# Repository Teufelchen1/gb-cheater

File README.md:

# gb-cheater
A gameboy(GB,GBC,GBA) reader/writer

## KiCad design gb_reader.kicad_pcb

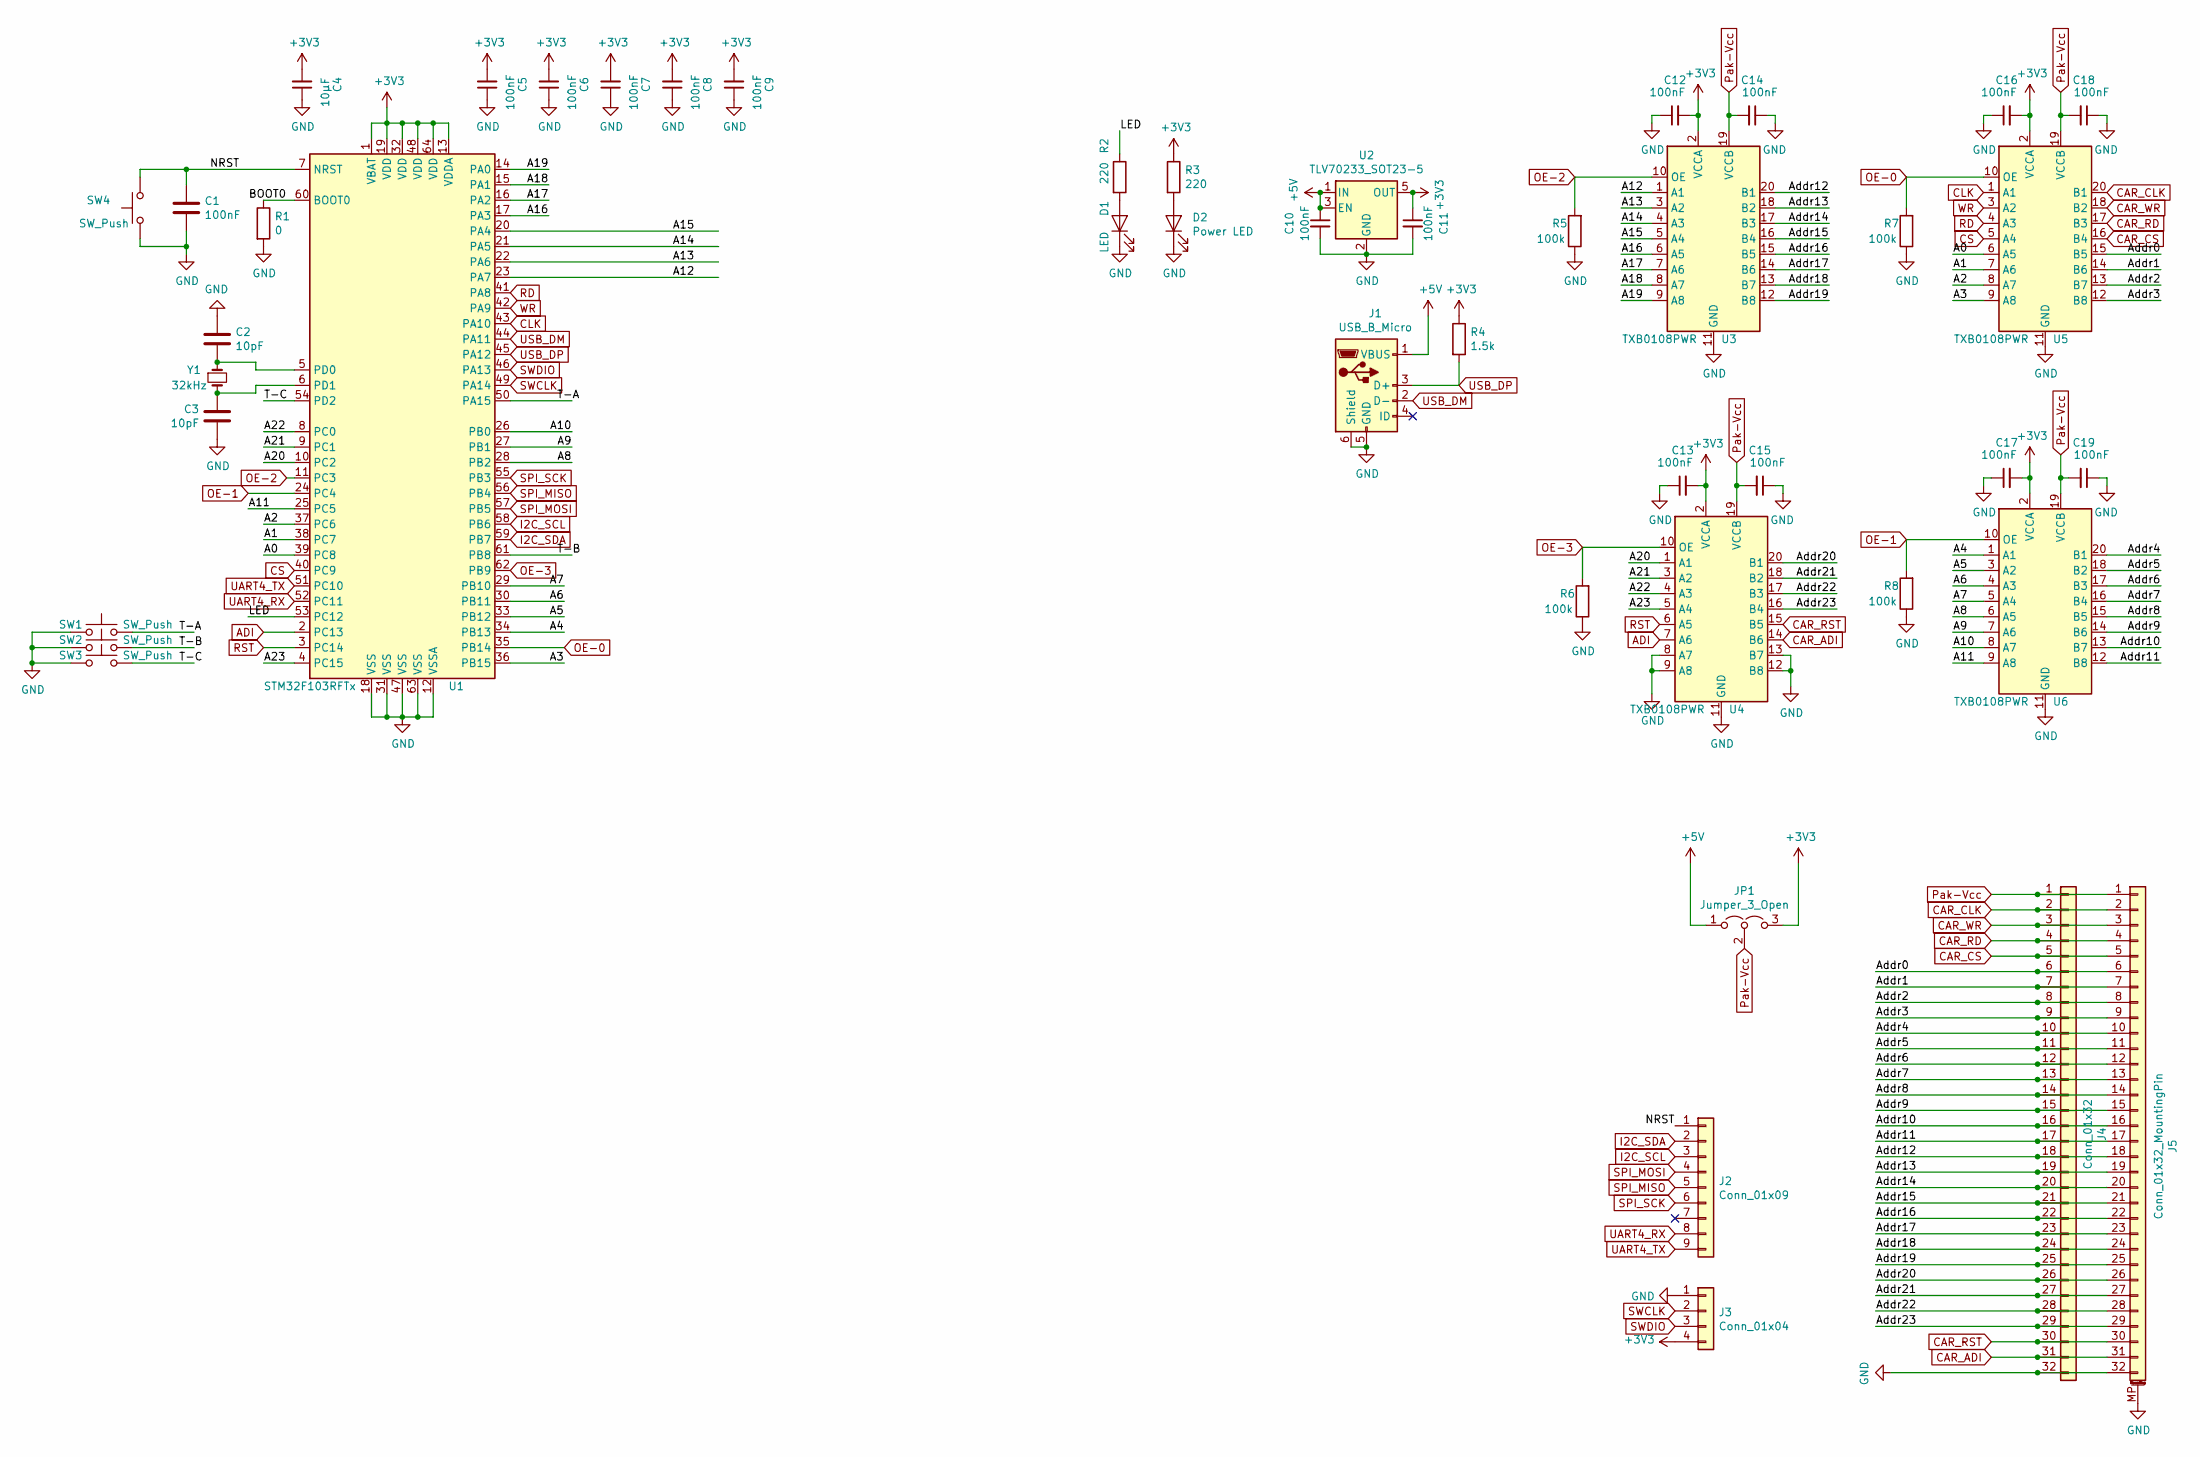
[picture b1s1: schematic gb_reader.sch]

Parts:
C1, C5, C6, C7, C8, C9, C10, C11, C12, C13, C14, C15, C16, C17, C18, C19: 100nF; C_0603_1608Metric
C2, C3: 10pF; C_0603_1608Metric
C4: 10µF; C_0603_1608Metric
D1: LED; LED_0805_2012Metric
D2: Power LED; LED_0805_2012Metric
J1: USB_B_Micro; USB_Micro-B_Molex_47346-0001
J2: Conn_01x09; PinHeader_1x09_P2.54mm_Horizontal
J3: Conn_01x04; PinHeader_1x04_P2.54mm_Horizontal
J4: Conn_01x32; PinHeader_2x16_P2.54mm_Vertical
J5: Conn_01x32_MountingPin; DSL_Cartridge_Reader
JP1: Jumper_3_Open; PinHeader_1x03_P2.54mm_Vertical
R1: 0; SolderJumper-2_P1.3mm_Open_TrianglePad1.0x1.5mm
R2, R3: 220; R_0603_1608Metric
R4: 1.5k; R_0603_1608Metric
R5, R6, R7, R8: 100k; R_0603_1608Metric
SW1, SW2, SW3, SW4: SW_Push; SW_Push_1P1T_NO_CK_KMR2
U1: STM32F103RFTx; LQFP-64_10x10mm_P0.5mm
U2: TLV70233_SOT23-5; SOT-23-5
U3, U4, U5, U6: TXB0108PWR; TSSOP-20_4.4x6.5mm_P0.65mm
Y1: 32kHz; Crystal_HC49-4H_Vertical

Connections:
+3V3: C4.2, C5.2, C6.2, C7.2, C8.2, C9.2, C11.1, C12.2, C13.2, C16.2, C17.2, J3.4, JP1.3 (B), R3.1, R4.1, U1.1 (VBAT), U1.13 (VDDA), U1.19 (VDD), U1.32 (VDD), U1.48 (VDD), U1.64 (VDD), U2.5 (OUT), U3.2 (VCCA), U4.2 (VCCA), U5.2 (VCCA), U6.2 (VCCA)
+5V: C10.1, J1.1 (VBUS), JP1.1 (A), U2.1 (IN), U2.3 (EN)
/A0: U1.39 (PC8), U5.6 (A5)
/A1: U1.38 (PC7), U5.7 (A6)
/A2: U1.37 (PC6), U5.8 (A7)
/A3: U1.36 (PB15), U5.9 (A8)
/A4: U1.34 (PB13), U6.1 (A1)
/A5: U1.33 (PB12), U6.3 (A2)
/A6: U1.30 (PB11), U6.4 (A3)
/A7: U1.29 (PB10), U6.5 (A4)
/A8: U1.28 (PB2), U6.6 (A5)
/A9: U1.27 (PB1), U6.7 (A6)
/A10: U1.26 (PB0), U6.8 (A7)
/A11: U1.25 (PC5), U6.9 (A8)
/A12: U1.23 (PA7), U3.1 (A1)
/A13: U1.22 (PA6), U3.3 (A2)
/A14: U1.21 (PA5), U3.4 (A3)
/A15: U1.20 (PA4), U3.5 (A4)
/A16: U1.17 (PA3), U3.6 (A5)
/A17: U1.16 (PA2), U3.7 (A6)
/A18: U1.15 (PA1), U3.8 (A7)
/A19: U1.14 (PA0), U3.9 (A8)
/A20: U1.10 (PC2), U4.1 (A1)
/A21: U1.9 (PC1), U4.3 (A2)
/A22: U1.8 (PC0), U4.4 (A3)
/A23: U1.4 (PC15), U4.5 (A4)
/Addr0: J4.6, J5.6, U5.15 (B5)
/Addr1: J4.7, J5.7, U5.14 (B6)
/Addr2: J4.8, J5.8, U5.13 (B7)
/Addr3: J4.9, J5.9, U5.12 (B8)
/Addr4: J4.10, J5.10, U6.20 (B1)
/Addr5: J4.11, J5.11, U6.18 (B2)
/Addr6: J4.12, J5.12, U6.17 (B3)
/Addr7: J4.13, J5.13, U6.16 (B4)
/Addr8: J4.14, J5.14, U6.15 (B5)
/Addr9: J4.15, J5.15, U6.14 (B6)
/Addr10: J4.16, J5.16, U6.13 (B7)
/Addr11: J4.17, J5.17, U6.12 (B8)
/Addr12: J4.18, J5.18, U3.20 (B1)
/Addr13: J4.19, J5.19, U3.18 (B2)
/Addr14: J4.20, J5.20, U3.17 (B3)
/Addr15: J4.21, J5.21, U3.16 (B4)
/Addr16: J4.22, J5.22, U3.15 (B5)
/Addr17: J4.23, J5.23, U3.14 (B6)
/Addr18: J4.24, J5.24, U3.13 (B7)
/Addr19: J4.25, J5.25, U3.12 (B8)
/Addr20: J4.26, J5.26, U4.20 (B1)
/Addr21: J4.27, J5.27, U4.18 (B2)
/Addr22: J4.28, J5.28, U4.17 (B3)
/Addr23: J4.29, J5.29, U4.16 (B4)
/BOOT0: R1.1, U1.60 (BOOT0)
/LED: R2.1, U1.53 (PC12)
/NRST: C1.1, J2.1, SW4.2, U1.7 (NRST)
/T-A: SW1.2, U1.50 (PA15)
/T-B: SW2.2, U1.61 (PB8)
/T-C: SW3.2, U1.54 (PD2)
ADI: U1.2 (PC13), U4.7 (A6)
CAR_ADI: J4.31, J5.31, U4.14 (B6)
CAR_CLK: J4.2, J5.2, U5.20 (B1)
CAR_CS: J4.5, J5.5, U5.16 (B4)
CAR_RD: J4.4, J5.4, U5.17 (B3)
CAR_RST: J4.30, J5.30, U4.15 (B5)
CAR_WR: J4.3, J5.3, U5.18 (B2)
CLK: U1.43 (PA10), U5.1 (A1)
CS: U1.40 (PC9), U5.5 (A4)
GND: C1.2, C2.2, C3.2, C4.1, C5.1, C6.1, C7.1, C8.1, C9.1, C10.2, C11.2, C12.1, C13.1, C14.1, C15.1, C16.1, C17.1, C18.1, C19.1, D1.1 (K), D2.1 (K), J1.5 (GND), J1.6 (Shield), J3.1, J4.32, J5.32, J5.MP (MountPin), R1.2, R5.1, R6.1, R7.1, R8.1, SW1.1, SW2.1, SW3.1, SW4.1, U1.12 (VSSA), U1.18 (VSS), U1.31 (VSS), U1.47 (VSS), U1.63 (VSS), U2.2 (GND), U3.11 (GND), U4.8 (A7), U4.9 (A8), U4.11 (GND), U4.12 (B8), U4.13 (B7), U5.11 (GND), U6.11 (GND)
I2C_SCL: J2.3, U1.58 (PB6)
I2C_SDA: J2.2, U1.59 (PB7)
unnamed: C2.1, U1.5 (PD0), Y1.1
unnamed: C3.1, U1.6 (PD1), Y1.2
unnamed: D1.2 (A), R2.2
unnamed: D2.2 (A), R3.2
OE-0: R7.2, U1.35 (PB14), U5.10 (OE)
OE-1: R8.2, U1.24 (PC4), U6.10 (OE)
OE-2: R5.2, U1.11 (PC3), U3.10 (OE)
OE-3: R6.2, U1.62 (PB9), U4.10 (OE)
Pak-Vcc: C14.2, C15.2, C18.2, C19.2, J4.1, J5.1, JP1.2 (C), U3.19 (VCCB), U4.19 (VCCB), U5.19 (VCCB), U6.19 (VCCB)
RD: U1.41 (PA8), U5.4 (A3)
RST: U1.3 (PC14), U4.6 (A5)
SPI_MISO: J2.5, U1.56 (PB4)
SPI_MOSI: J2.4, U1.57 (PB5)
SPI_SCK: J2.6, U1.55 (PB3)
SWCLK: J3.2, U1.49 (PA14)
SWDIO: J3.3, U1.46 (PA13)
UART4_RX: J2.8, U1.52 (PC11)
UART4_TX: J2.9, U1.51 (PC10)
USB_DM: J1.2 (D-), U1.44 (PA11)
USB_DP: J1.3 (D+), R4.2, U1.45 (PA12)
WR: U1.42 (PA9), U5.3 (A2)

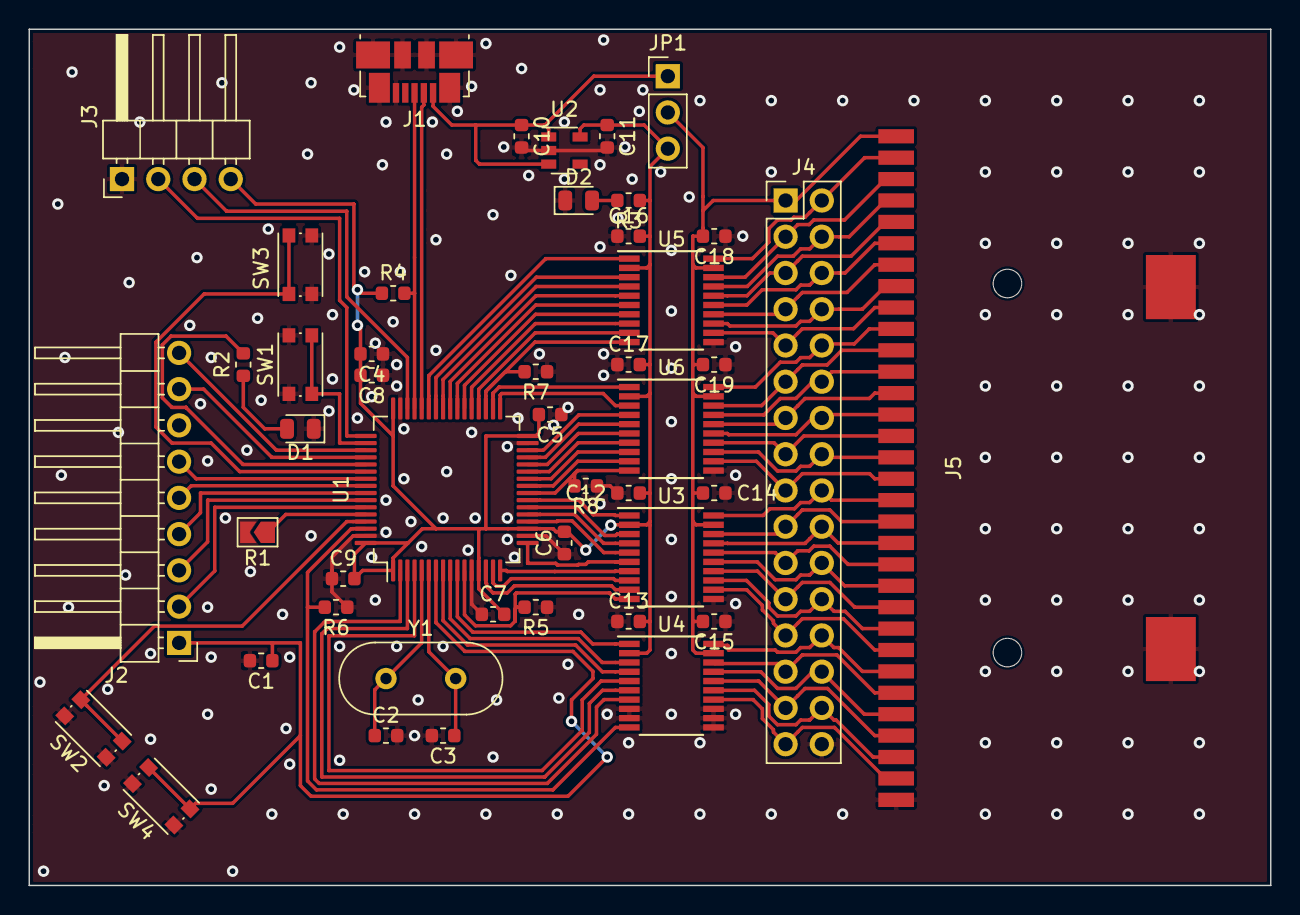
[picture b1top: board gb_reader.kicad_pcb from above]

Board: 2 copper layers, 87.0 x 60.0 mm, 46 parts (0 on the bottom side), 89 nets.

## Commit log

2019-08-11 pcb layouting
2019-08-13 Done...löl
2019-08-13 fixed pcb outline
2019-08-13 new size
2019-08-23 old header
2019-08-24 Done
2019-10-30 updated pcb
